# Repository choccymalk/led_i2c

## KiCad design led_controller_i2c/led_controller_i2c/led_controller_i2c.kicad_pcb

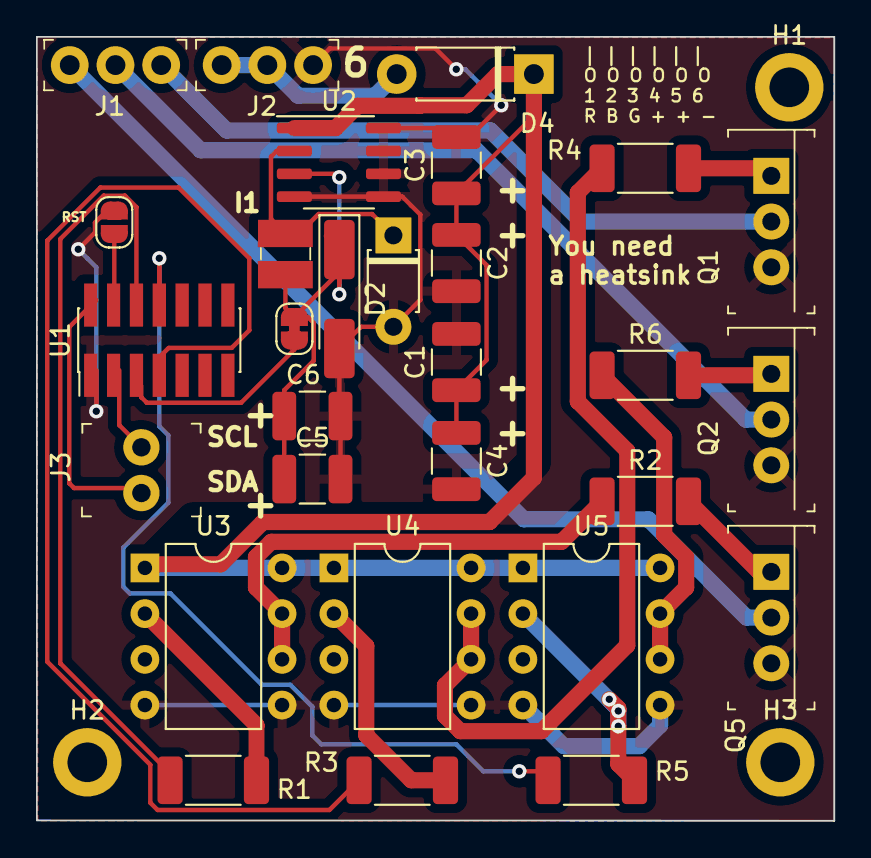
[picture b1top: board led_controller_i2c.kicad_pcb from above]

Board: 2 copper layers, 44.3 x 43.5 mm, 32 parts (0 on the bottom side), 24 nets.

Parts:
C1, C4, C6: C; C_1210_3225Metric_Pad1.33x2.70mm_HandSolder
C2, C3, C5: C_Polarized_US; C_1210_3225Metric_Pad1.33x2.70mm_HandSolder
D1: D_Schottky; D_T-1_P5.08mm_Horizontal
D2: ZMMxx; D_MiniMELF_Handsoldering
D4: 1N4002; D_DO-41_SOD81_P7.62mm_Horizontal
H1, H2, H3: MountingHole; MountingHole_2.2mm_M2_DIN965_Pad
J1, J2: 640456-3; PinHeader_1x3_P2.54_Drill1.1mm
J3: 640456-2; PinHeader_1x2_P2.54mm_Drill1.02mm
JP1: SolderJumper_2_Bridged; SolderJumper-2_P1.3mm_Bridged_RoundedPad1.0x1.5mm
JP2: SolderJumper_2_Open; SolderJumper-2_P1.3mm_Open_RoundedPad1.0x1.5mm
L1: 82473C; 1210
Q1, Q2, Q5: IRF540NPBF; TO-220-3
R1, R2, R3, R4, R5, R6: R_US; R_2010_5025Metric_Pad1.40x2.65mm_HandSolder
U1: STM32F030F4P6; PinHeader_2x07_P1.27mm_Vertical_SMD
U2: XL1509-3.3; SOIC-8_3.9x4.9mm_P1.27mm
U3, U4, U5: TC4422; DIP-8_W7.62mm

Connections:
GND: C1.2, C2.2, C3.2, C4.2, C5.2, C6.2, D1.2 (A), D2.2 (A), J2.1, JP2.1 (A), Q1.3 (S), Q2.3 (S), Q5.3 (S), U1.1 (BOOT0), U2.4 (~EN), U2.5 (GND), U2.6 (GND), U2.7 (GND), U2.8 (GND), U3.4 (GND), U3.5 (GND), U4.4 (GND), U4.5 (GND), U5.4 (GND), U5.5 (GND)
unnamed: D1.1 (K), L1.1, U2.2 (OUT)
unnamed: C5.1, C6.1, D2.1 (K), JP1.1 (A), L1.2, U2.3 (FB)
unnamed: D4.2 (A), J2.2, J2.3
unnamed: JP1.2 (B), U1.5 (VDDA)
unnamed: JP2.2 (B), U1.4 (NRST)
unnamed: Q1.1 (G), R4.2
unnamed: Q2.1 (G), R6.2
unnamed: Q5.1 (G), R2.2
unnamed: R2.1, U3.6 (OUTPUT), U3.7 (OUTPUT)
unnamed: R4.1, U4.6 (OUTPUT), U4.7 (OUTPUT)
unnamed: R6.1, U5.6 (OUTPUT), U5.7 (OUTPUT)
unnamed: R1.1, U1.6 (PA0)
unnamed: R3.1, U1.7 (PA1)
unnamed: R5.1, U1.8 (PA2)
unnamed: J3.1, U1.2 (PF0)
unnamed: J3.2, U1.3 (PF1)
unnamed: R1.2, U3.2 (INPUT)
unnamed: R3.2, U4.2 (INPUT)
unnamed: R5.2, U5.2 (INPUT)
b: J1.2, Q2.2 (D)
g: J1.1, Q1.2 (D)
r: J1.3, Q5.2 (D)
vin: C1.1, C2.1, C3.1, C4.1, D4.1 (K), U2.1 (VIN), U3.1 (VDD), U3.8 (VDD), U4.1 (VDD), U4.8 (VDD), U5.1 (VDD), U5.8 (VDD)

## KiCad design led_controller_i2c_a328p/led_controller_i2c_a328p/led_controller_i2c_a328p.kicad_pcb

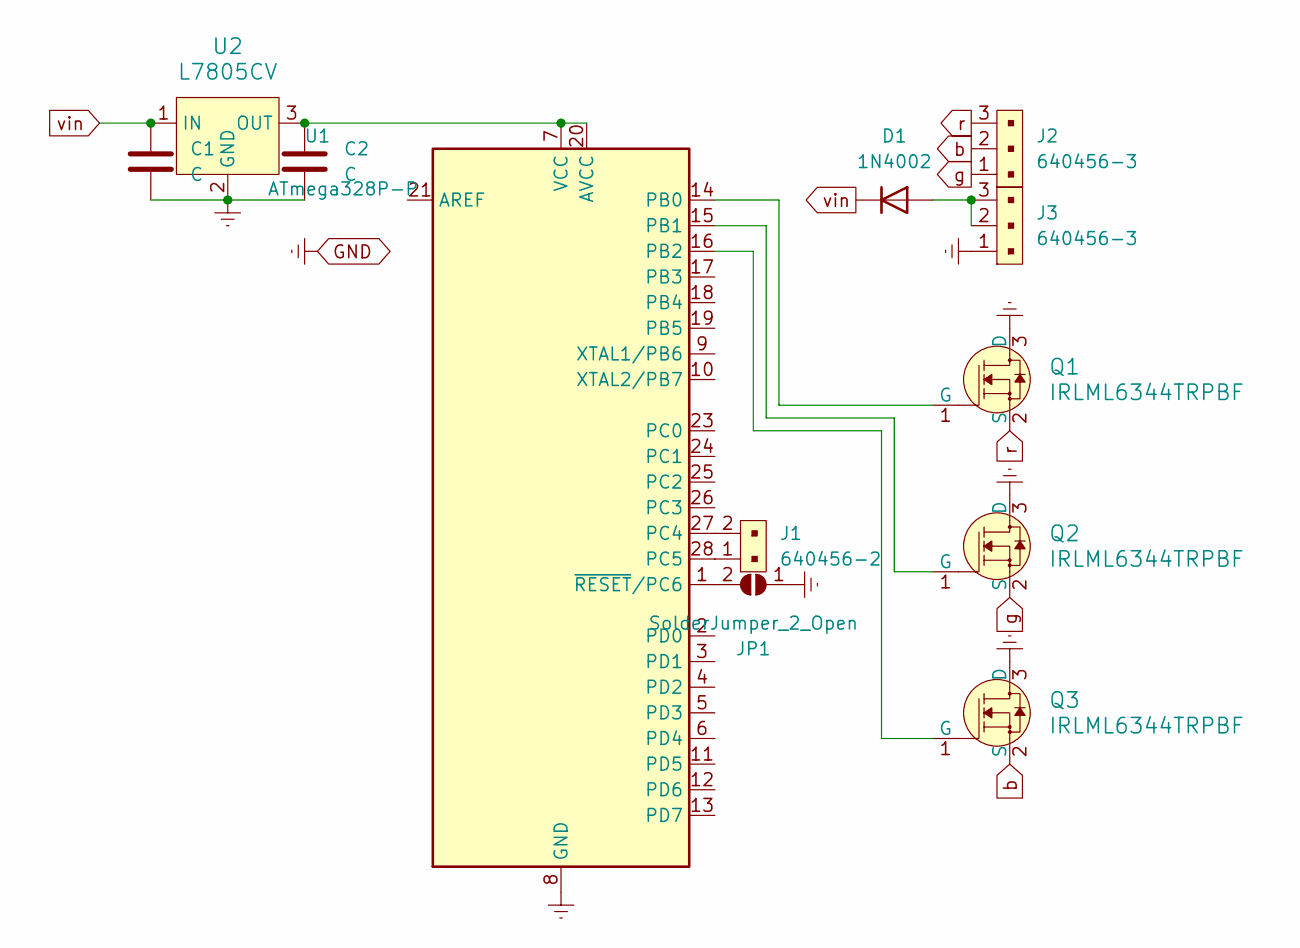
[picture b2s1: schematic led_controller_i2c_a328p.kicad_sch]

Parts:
C1, C2: C; CP_EIA-3528-21_Kemet-B_Pad1.50x2.35mm_HandSolder
D1: 1N4002; D_DO-41_SOD81_P7.62mm_Horizontal
J1: 640456-2; PinHeader_1x2_P2.54mm_Drill1.02mm; MPN 640456-2; Digi-Key_PN A1921-ND
J2, J3: 640456-3; PinHeader_1x3_P2.54_Drill1.1mm; MPN 640456-3; Digi-Key_PN A19470-ND
JP1: SolderJumper_2_Open; SolderJumper-2_P1.3mm_Open_RoundedPad1.0x1.5mm
Q1, Q2, Q3: IRLML6344TRPBF; SOT-23-3; MPN IRLML6344TRPBF; Digi-Key_PN IRLML6344TRPBFCT-ND
U1: ATmega328P-P; DIP-28_W7.62mm
U2: L7805CV; TO-220-3; MPN L7805CV; Digi-Key_PN 497-1443-5-ND

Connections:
GND: C1.2, C2.2, J3.1, JP1.1 (A), Q1.3 (D), Q2.3 (D), Q3.3 (D), U1.8 (GND), U1.22 (GND), U2.2 (GND)
unnamed: D1.2 (A), J3.2, J3.3
unnamed: JP1.2 (B), U1.1 (~RESET/PC6)
unnamed: Q1.1 (G), U1.14 (PB0)
unnamed: Q2.1 (G), U1.15 (PB1)
unnamed: Q3.1 (G), U1.16 (PB2)
unnamed: C2.1, U1.7 (VCC), U1.20 (AVCC), U2.3 (OUT)
unnamed: J1.2, U1.27 (PC4)
unnamed: J1.1, U1.28 (PC5)
b: J2.2, Q3.2 (S)
g: J2.1, Q2.2 (S)
r: J2.3, Q1.2 (S)
vin: C1.1, D1.1 (K), U2.1 (IN)

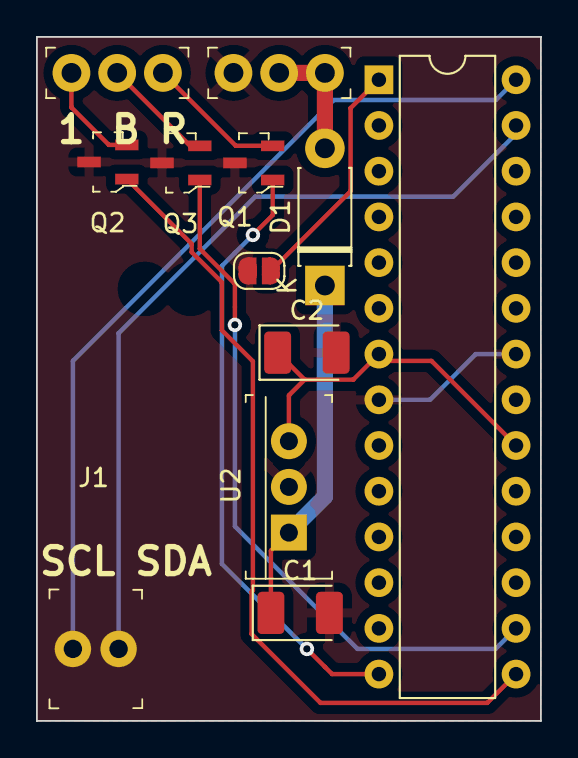
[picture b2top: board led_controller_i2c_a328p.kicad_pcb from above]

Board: 2 copper layers, 28.0 x 38.0 mm, 12 parts (0 on the bottom side), 13 nets.
